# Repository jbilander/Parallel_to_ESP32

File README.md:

# Parallel_to_ESP32
A parallel to ESP32 project for the Amiga

***

This carrier board is made to host the popular ESP32-DEVKIT-V1 board widely available for a few bucks on AliExpress and the likes. Powering the board can be done by taking +5V from the Amigas external floppy drive port using an [Adapter](https://github.com/jbilander/Amiga_DB23_to_USB_C_power_only_adapter) and connect to the DEVKIT's Micro-USB jack.

A FileServer firmware is being developed and is available here:<br />
https://github.com/jbilander/ESP32-FileServer

***

<br />

***

Revision 1A
<br />

<br />

<br />

<br />

***

BOM Rev. 1A
---------
Designator  | Name/Value   | Package | Notes
-|-|-|-|
U1 | ESP32-DEVKIT-V1 | DIP-30 | Please note tested variant is Type/Color: <br />[ESP32-CP2102-MICRO](https://www.aliexpress.com/item/1005004337178335.html)
U2 | SN74CB3T16210DGGR | TSSOP-48  | [SN74CB3T16210DGGR](https://www.mouser.com/ProductDetail/595-SN74CB3T16210DGG)
J1 | D-Sub DB25 Male connector | EdgeMount, parallel port connector solder type | [D-Sub DB25M](https://www.aliexpress.com/item/32974759586.html)
J2 | Sunrom Micro SD Card Holder | 9-pin Micro SD card slot connector | [Sunrom Micro-SD card holder](https://www.aliexpress.com/item/32802051702.html)
J3 | PinHeader 2x02 | EdgeMount, PinHeader_2x02_P2.54mm | UART1 connector PADs with 3V3/GND Power connectors on the underside for external powering a [RS-232 device](https://www.aliexpress.com/item/1005001685534114.html) or similar from the ESP32
J4 | PinHeader 2x02 | EdgeMount, PinHeader_2x02_P2.54mm | UART2 connector PADs with 3V3/GND Power connectors on the underside for external powering a [RS-232 device](https://www.aliexpress.com/item/1005001685534114.html) or similar from the ESP32
R1 | ~150 Ω Resistor | 0805, 200 mW | (Mandatory if D1 populated) Series resistor for D1 LED, adjust R-value to your type of LED and preferred brightness
R2 | ~150 Ω Resistor | 0805, 200 mW | (Mandatory if D2 populated) Series resistor for D2 LED, adjust R-value to your type of LED and preferred brightness
R3,R4,R6,R7 | LED Resistor 1k Ω | 0603 | [RC0603FR-071KL](https://www.mouser.com/ProductDetail/603-RC0603FR-071KL)
R5 | Resistor 10k or 4.7k Ω | 0603 | Pull-up resistor for Card Present/Detect, signal grounded when card is present in socket
R8 | Resistor 4.7k Ω or 10k Ω | 0603 | Pull-up resistor (on 5V side) for /STROBE-signal <br />[RC0603FR-074K7L](https://www.mouser.com/ProductDetail/603-RC0603FR-074K7L)
RN1-RN3 | CAY16-4701F4LF Resistor pack 4.7k or 10k Ω (CAY16-103J4LF) | 1206 | [CAY16-4701F4LF](https://www.mouser.com/ProductDetail/652-CAY16A-4701F4LF) Optional Pull-up resistors for Signals: ACK,BUSY,POUT,SELECT,Data0-Data7
D1 (Optional) | LED 3mm | PinHeader_1x02_P2.54mm_Vertical, pin pitch 2.54 mm | [Activity LED indicator](https://www.aliexpress.com/item/1005001688927024.html) (Diffused Orange / Amber or whatever colour you prefer)
D2 (Optional) | LED 3mm | PinHeader_1x02_P2.54mm_Vertical, pin pitch 2.54 mm | [Power LED indicator](https://www.aliexpress.com/item/1005001688927024.html) (Green Diffused or whatever colour you prefer)
D3-D6 | SMD LED | 0603 | [SMD LED 0603](https://www.aliexpress.com/item/1005003836509392.html)
C1-C4 | Capacitor 0.1uF = 100nF | 0805 |
JP1 (Optional) | PinHeader 1x02 | PinHeader_1x02_P2.54mm_Vertical | Shunt on to enable reset ESP32 in conjunction with Ctrl-Amiga-Amiga, Please Note pressing the RESET-button on the ESP32 will also assert the Amiga-RESET, be careful, know what you're doing if you enable this one.

***

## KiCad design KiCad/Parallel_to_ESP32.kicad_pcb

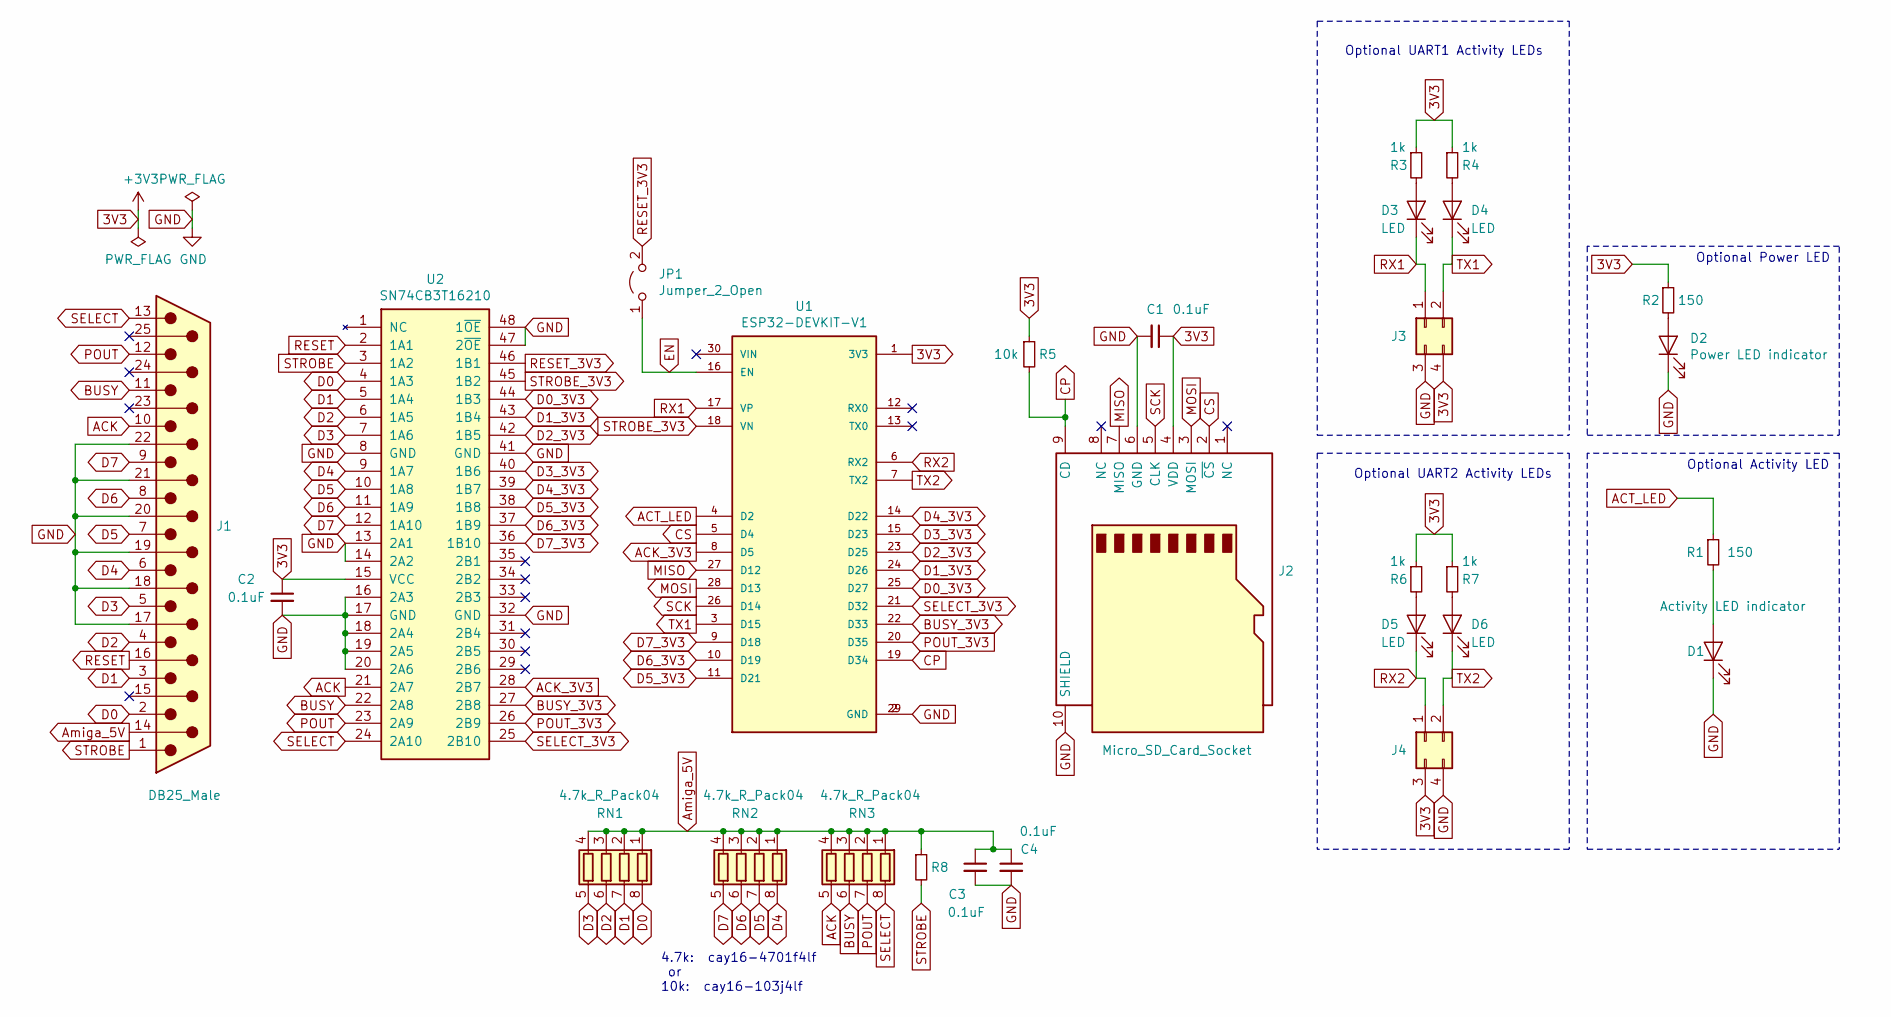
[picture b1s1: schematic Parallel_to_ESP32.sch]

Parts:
C1, C2, C3, C4: 0.1uF; C_0805_2012Metric_Pad1.15x1.40mm_HandSolder
D1: Activity LED indicator; LED_D3.0mm
D2: Power LED indicator; LED_D3.0mm
D3, D4, D5, D6: LED; D_0603_1608Metric_Pad1.05x0.95mm_HandSolder
J1: DB25_Male; DSUB-25_Male_EdgeMount_P2.77mm
J2: Micro_SD_Card_Socket; GCT-MEM2055-00-190-01-A
J3, J4: Conn_02x02_Top_Bottom; PinHeader_2x02_P2.54mm_EdgeMount_SMD
JP1: Jumper_2_Open; PinHeader_1x02_P2.54mm_Vertical
R1, R2: 150; R_0805_2012Metric_Pad1.15x1.40mm_HandSolder
R3, R4, R6, R7: 1k; R_0603_1608Metric_Pad1.05x0.95mm_HandSolder
R5, R8: 10k; R_0603_1608Metric_Pad1.05x0.95mm_HandSolder
RN1, RN2, RN3: 4.7k_R_Pack04; RESCAF80P320X160X60-8N
U1: ESP32-DEVKIT-V1; MODULE_ESP32_DEVKIT_V1; PARTREV N/A
U2: SN74CB3T16210; TSSOP-48_6.1x12.5mm_P0.5mm

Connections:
3V3: C1.1, C2.1, J2.4 (VDD), J3.4, J4.3, R2.1, R3.1, R4.1, R5.1, R6.1, R7.1, U1.1 (3V3), U2.15 (VCC)
ACK: J1.10, RN3.5 (R4.2), U2.21 (2A7)
ACK_3V3: U1.8 (D5), U2.28 (2B7)
ACT_LED: R1.1, U1.4 (D2)
Amiga_5V: C3.1, C4.1, J1.14, R8.1, RN1.1 (R1.1), RN1.2 (R2.1), RN1.3 (R3.1), RN1.4 (R4.1), RN2.1 (R1.1), RN2.2 (R2.1), RN2.3 (R3.1), RN2.4 (R4.1), RN3.1 (R1.1), RN3.2 (R2.1), RN3.3 (R3.1), RN3.4 (R4.1)
BUSY: J1.11, RN3.6 (R3.2), U2.22 (2A8)
BUSY_3V3: U1.22 (D33), U2.27 (2B8)
CP: J2.9 (CD), R5.2, U1.19 (D34)
CS: J2.2 (~CS), U1.5 (D4)
D0: J1.2, RN1.8 (R1.2), U2.4 (1A3)
D0_3V3: U1.25 (D27), U2.44 (1B3)
D1: J1.3, RN1.7 (R2.2), U2.5 (1A4)
D1_3V3: U1.24 (D26), U2.43 (1B4)
D2: J1.4, RN1.6 (R3.2), U2.6 (1A5)
D2_3V3: U1.23 (D25), U2.42 (1B5)
D3: J1.5, RN1.5 (R4.2), U2.7 (1A6)
D3_3V3: U1.15 (D23), U2.40 (1B6)
D4: J1.6, RN2.8 (R1.2), U2.9 (1A7)
D4_3V3: U1.14 (D22), U2.39 (1B7)
D5: J1.7, RN2.7 (R2.2), U2.10 (1A8)
D5_3V3: U1.11 (D21), U2.38 (1B8)
D6: J1.8, RN2.6 (R3.2), U2.11 (1A9)
D6_3V3: U1.10 (D19), U2.37 (1B9)
D7: J1.9, RN2.5 (R4.2), U2.12 (1A10)
D7_3V3: U1.9 (D18), U2.36 (1B10)
EN: JP1.1 (A), U1.16 (EN)
GND: C1.2, C2.2, C3.2, C4.2, D1.1 (K), D2.1 (K), J1.17, J1.18, J1.19, J1.20, J1.21, J1.22, J2.6 (GND), J2.10 (SHIELD), J3.3, J4.4, U1.2 (GND), U1.29 (GND), U2.8 (GND), U2.13 (2A1), U2.14 (2A2), U2.16 (2A3), U2.17 (GND), U2.18 (2A4), U2.19 (2A5), U2.20 (2A6), U2.32 (GND), U2.41 (GND), U2.47 (2~OE), U2.48 (1~OE)
MISO: J2.7 (MISO), U1.27 (D12)
MOSI: J2.3 (MOSI), U1.28 (D13)
unnamed: D1.2 (A), R1.2
unnamed: D2.2 (A), R2.2
unnamed: D3.2 (A), R3.2
unnamed: D4.2 (A), R4.2
unnamed: D5.2 (A), R6.2
unnamed: D6.2 (A), R7.2
POUT: J1.12, RN3.7 (R2.2), U2.23 (2A9)
POUT_3V3: U1.20 (D35), U2.26 (2B9)
RESET: J1.16, U2.2 (1A1)
RESET_3V3: JP1.2 (B), U2.46 (1B1)
RX1: D3.1 (K), J3.1, U1.17 (VP)
RX2: D5.1 (K), J4.1, U1.6 (RX2)
SCK: J2.5 (CLK), U1.26 (D14)
SELECT: J1.13, RN3.8 (R1.2), U2.24 (2A10)
SELECT_3V3: U1.21 (D32), U2.25 (2B10)
STROBE: J1.1, R8.2, U2.3 (1A2)
STROBE_3V3: U1.18 (VN), U2.45 (1B2)
TX1: D4.1 (K), J3.2, U1.3 (D15)
TX2: D6.1 (K), J4.2, U1.7 (TX2)

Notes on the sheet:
Optional Activity LED
Optional Power LED
Optional UART1 Activity LEDs
Optional UART2 Activity LEDs
4.7k: cay16-4701f4lf or 10k: cay16-103j4lf

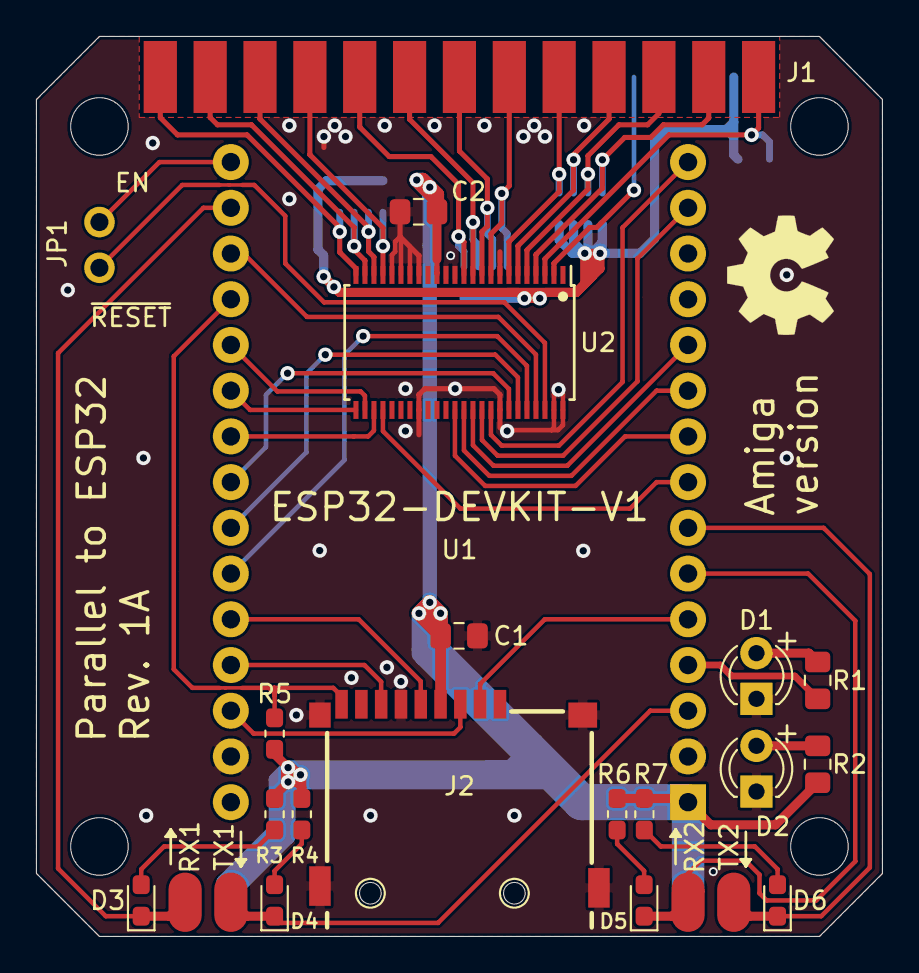
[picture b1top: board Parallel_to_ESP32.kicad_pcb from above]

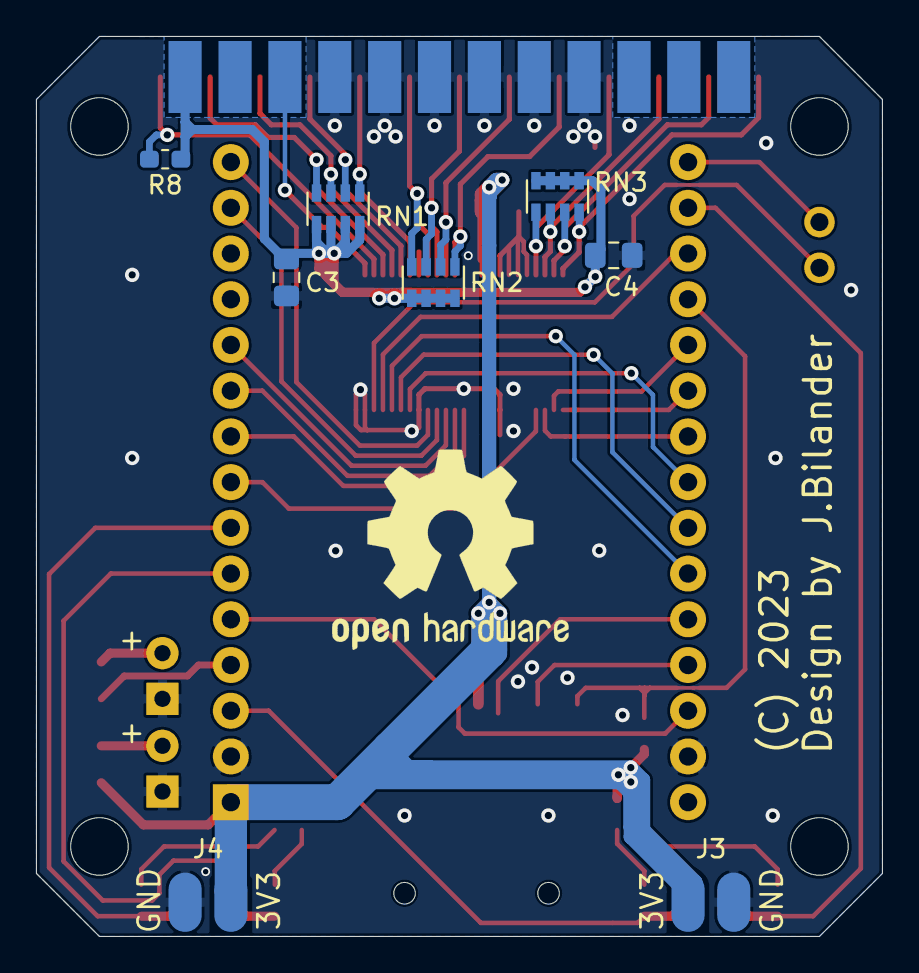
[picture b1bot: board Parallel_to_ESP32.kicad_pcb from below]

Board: 2 copper layers, 47.0 x 50.0 mm, 28 parts (6 on the bottom side), 48 nets.

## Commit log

2023-04-02 Create LICENSE
2023-04-02 Added KiCAD-files
2023-04-03 placing of components and some routing done
2023-04-03 more routing done
2023-04-03 Added Schematic for ESP32 Devkit V1 (DOIT)
2023-04-03 Removed JP
2023-04-03 more pin assignments and routing
2023-04-04 Added pinheader for UART1
2023-04-04 Added pinheader for UART2
2023-04-05 Changed R2 resistor to 0805-footprint and did some routing fixes
2023-04-05 fixed activity LED circuit using a PNP-transistor
2023-04-06 Re-assignment of some pins and simplified Activity LED circuit
2023-04-06 Added jumper JP1 for RESET-signal (optional)
2023-04-06 Added footprint
2023-04-06 Changed to surface mount footprint for UART1 and UART2 and 3V3/GND on underside, changed JP1 to regular PinHeader P2.54mm
2023-04-08 Added optional pull-up resistor packs for all Parallel-port-signals pulled up by Amigas 5V (pin 14)
2023-04-08 Added 3D-models
2023-04-08 Added 3D-model for ESP32-DEVKIT-V1
2023-04-11 Added OSHW-silkscreen logos
2023-04-11 Added 3D-model for D-sub DB25 male connector
2023-04-11 Added 3D-model of DB25 to the design
2023-04-11 Added 3D-screenshots
2023-04-11 Changed pull-up resistor packs to value 4.7k (cay16-4701f4lf)
2023-04-11 Rev1A schematic pdf
2023-06-15 Added files

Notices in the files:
KiCad/Parallel_to_ESP32.kicad_pcb:
(C) 2023
